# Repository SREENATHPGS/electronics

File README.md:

# electronics

This repo is will host my electronics designs released under public doman. Pleaes be cautious while implement the projects. Proceed if you know what you are doing!

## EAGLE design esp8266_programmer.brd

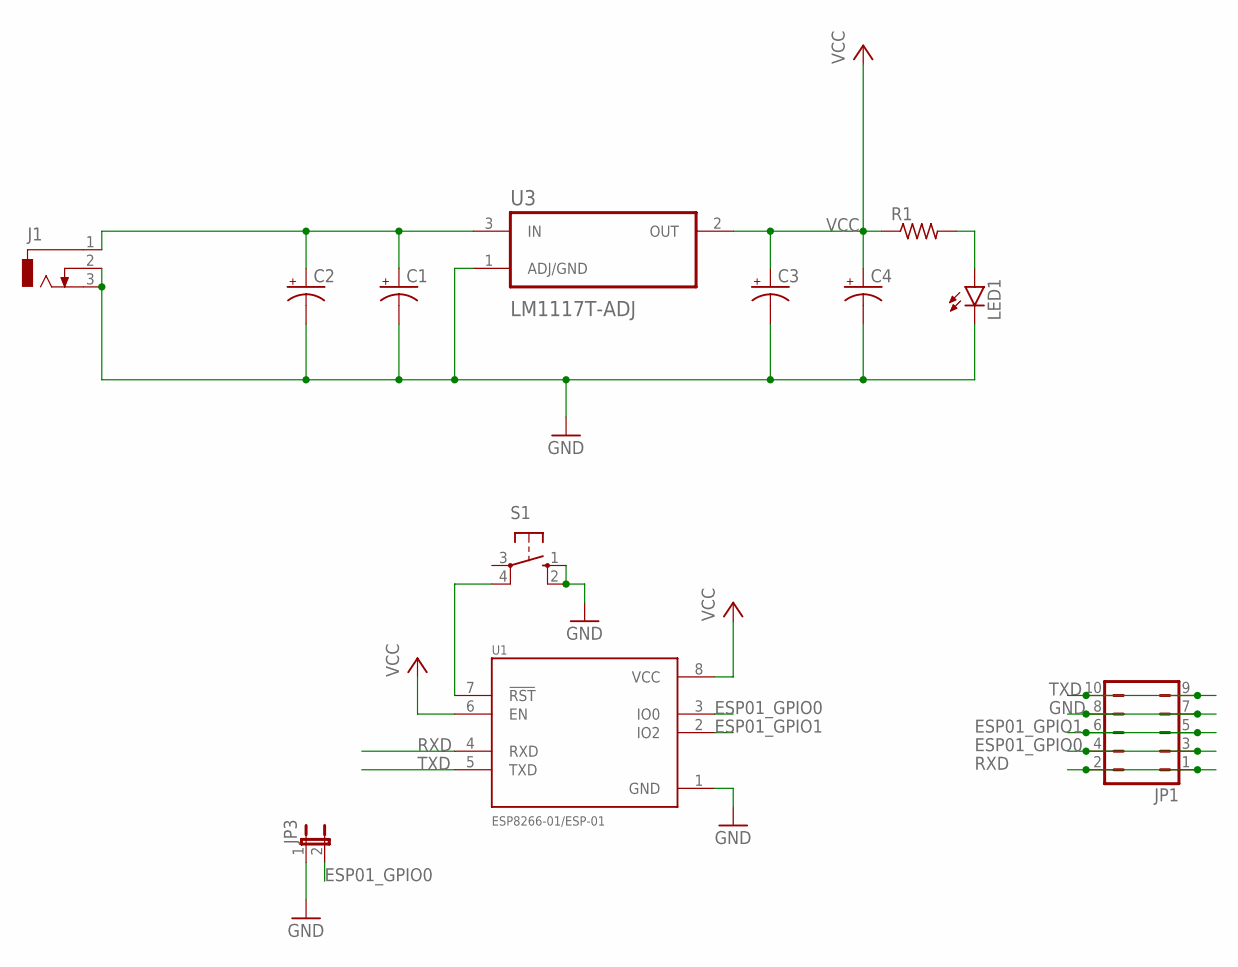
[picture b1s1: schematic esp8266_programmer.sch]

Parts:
C1, C2, C3, C4: CPOL-USE1.8-4; E1,8-4
J1: DCJ0303
JP1: JP5Q
JP3: JP1E; JP1
LED1: LED3MM
R1: R-US_0204/7; 0204/7
S1: 10-XX; B3F-10XX
U1: ESP8266-01/ESP-01; XCVR_ESP8266-01/ESP-01
U3: LM1117T-ADJ; TO254P1054X470X1955-3

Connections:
ESP01_GPIO0: JP1.3, JP1.4, JP3.2, U1.3 (IO0)
ESP01_GPIO1: JP1.5, JP1.6, U1.2 (IO2)
GND: C1.-, C2.-, C3.-, C4.-, J1.2, J1.3, JP1.7, JP1.8, JP3.1, LED1.K (C), S1.1 (S), S1.2 (S1), U1.1 (GND), U3.1 (ADJ/GND)
unnamed: C1.+, C2.+, J1.1, U3.3 (IN)
unnamed: S1.4 (P1), U1.7 (!RST)
unnamed: LED1.A, R1.2
RXD: JP1.1, JP1.2, U1.4 (RXD)
TXD: JP1.9, JP1.10, U1.5 (TXD)
VCC: C3.+, C4.+, R1.1, U1.6 (EN), U1.8 (VCC), U3.2 (OUT)

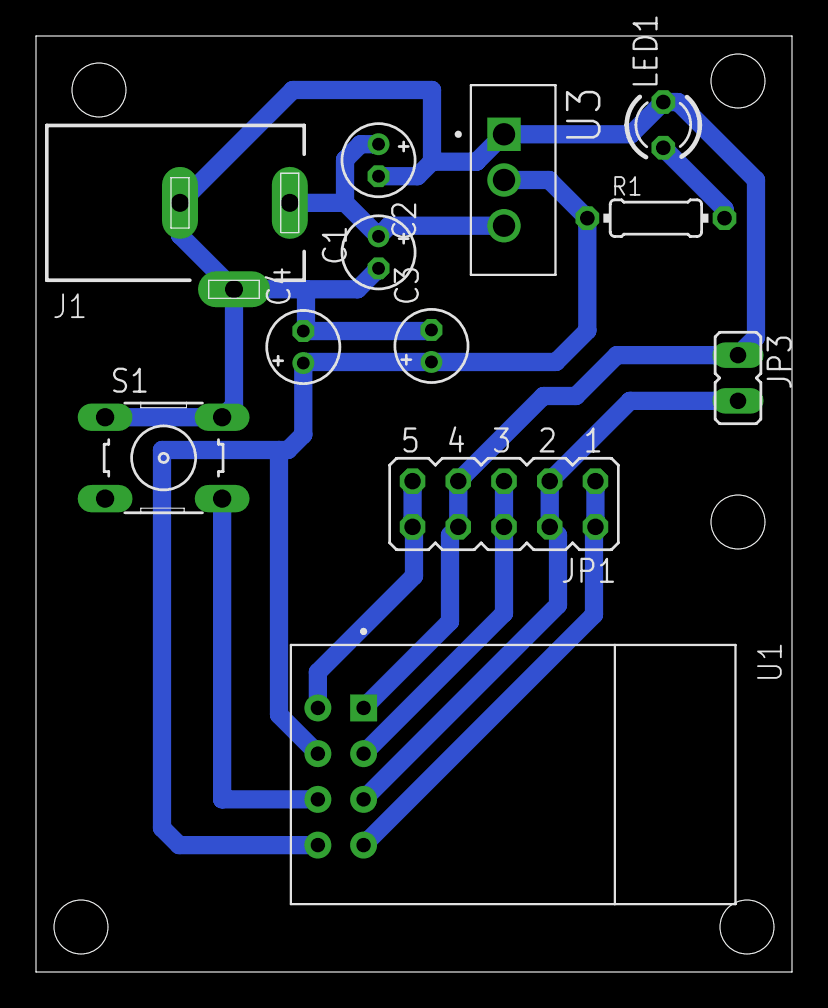
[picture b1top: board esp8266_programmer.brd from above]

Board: 2 copper layers, 42.0 x 52.0 mm, 12 parts (0 on the bottom side), 9 nets.

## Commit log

2024-08-14 added files
